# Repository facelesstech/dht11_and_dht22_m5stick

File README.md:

# dht11_and_dht22_m5stick
dht11_and_dht22_m5stick

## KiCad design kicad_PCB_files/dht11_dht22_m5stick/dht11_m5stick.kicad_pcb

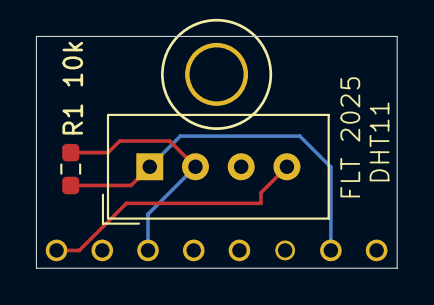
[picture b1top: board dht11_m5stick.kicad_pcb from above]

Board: 2 copper layers, 20.0 x 12.9 mm, 4 parts (0 on the bottom side), 3 nets.

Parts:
R1 10k: R; R_0603_1608Metric_Pad0.98x0.95mm_HandSolder
TP1: TestPoint; m3_hole_custom
U1: m5_stick_header_full
U2: DHT11; Aosong_DHT11_5.5x12.0_P2.54mm

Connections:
unnamed: R1 10k.2, U1.7 (3V3), U2.1 (VDD)
unnamed: R1 10k.1, U1.3 (G26), U2.2 (DATA)
unnamed: U1.1 (GND), U2.4 (GND)

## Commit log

2025-10-04 first upload of arduino code
2025-10-04 License added
2025-10-05 Kicad 9 PCB files
2025-10-05 Added the stl and the freecad files for both the dht11 and dht22
2025-10-05 removed the percent battery indicator because it wasnt working
